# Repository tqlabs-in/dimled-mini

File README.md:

<p align="center">
  <a href="https://github.com/tqlabs-in/dimled-mini">
    <picture>
      <source srcset="assets/logo-dark.png" media="(prefers-color-scheme: dark)">
      <source srcset="assets/logo-light.png" media="(prefers-color-scheme: light)">
      
    </picture>
  </a>
</p>

<p align="center"><q style="font-style: italic; font-weight: bold;"> Open Source PWM LED Dimmer powered by ESPHome </q></p>
<p align="center">
  <a href=""></img></a>
  
</p>

## 😎 Product Photography

## 🎰 PCB Renders

## 🧲 Useful Links

- [Web Flasher](https://tqlabs-in.github.io/dimled-mini/)
- [BOM](https://htmlpreview.github.io/?https://raw.githubusercontent.com/tqlabs-in/dimled-mini/main/pcb/bom/ibom.html)

## 🍀 Show your Support

Give a ⭐️ if this project helped you or you find it interesting!

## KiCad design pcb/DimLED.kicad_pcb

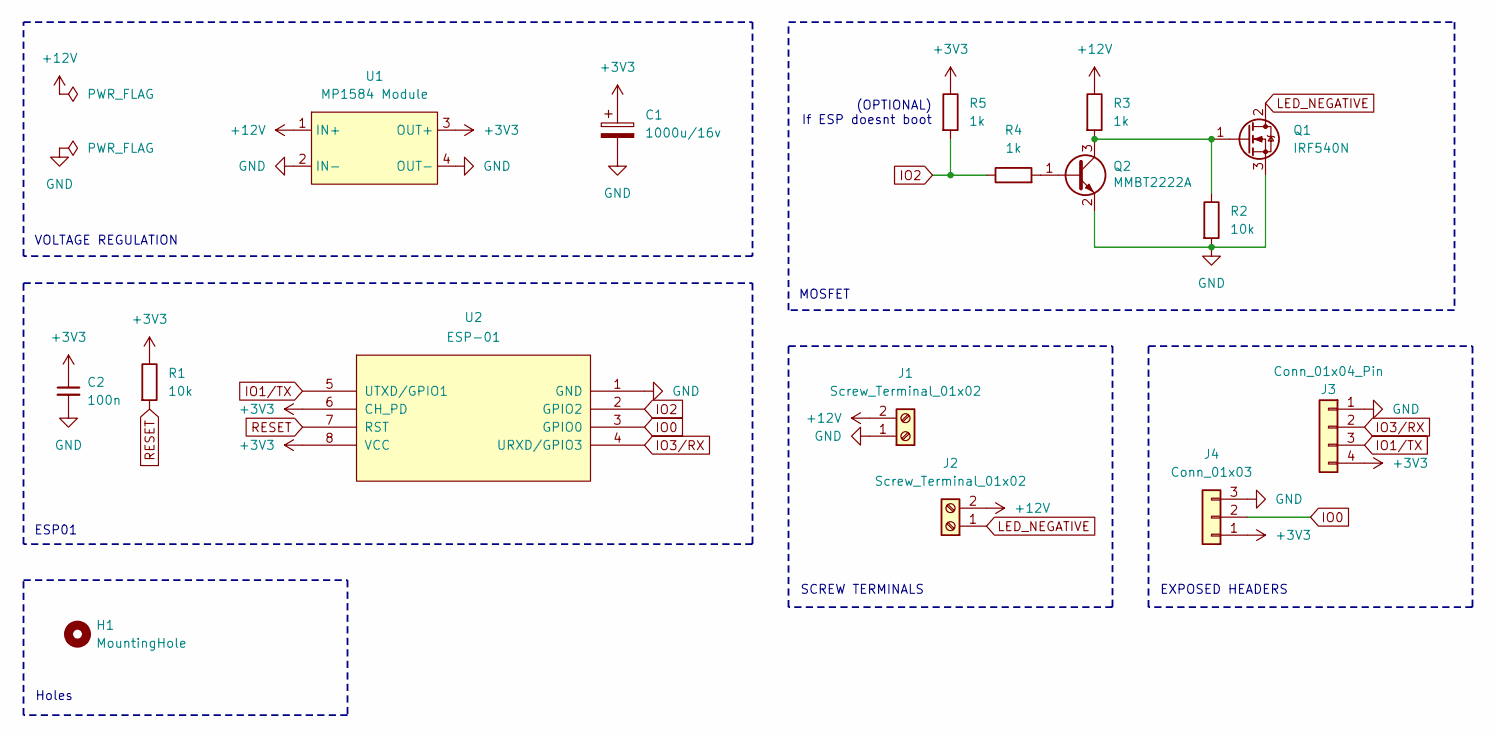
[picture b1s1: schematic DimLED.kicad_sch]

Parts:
C1: 1000u/16v; CP_Radial_D8.0mm_P3.50mm
C2: 100n; C_0805_2012Metric_Pad1.18x1.45mm_HandSolder
H1: MountingHole; ToolingHole_1.152mm
J1, J2: Screw_Terminal_01x02; TerminalBlock_bornier-2_P5.08mm
J3: Conn_01x04_Pin; PinSocket_1x04_P2.54mm_Vertical
J4: Conn_01x03; PinHeader_1x03_P2.54mm_Vertical
Q1: IRF540N; TO-220-3_Vertical
Q2: MMBT2222A; SOT-23
R1, R2: 10k; R_0805_2012Metric_Pad1.20x1.40mm_HandSolder
R3: 1k; R_Axial_DIN0309_L9.0mm_D3.2mm_P2.54mm_Vertical
R4, R5: 1k; R_0805_2012Metric_Pad1.20x1.40mm_HandSolder
U1: MP1584 Module; MP1584-Module_22.1x16.8mm_THT
U2: ESP-01; ESP-01_With_Headers

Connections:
+3V3: C1.1, C2.1, J3.4, J4.1, R1.1, R5.1, U1.3 (OUT+), U2.6 (CH_PD), U2.8 (VCC)
+12V: J1.2, J2.2, R3.1, U1.1 (IN+)
GND: C1.2, C2.2, J1.1, J3.1, J4.3, Q1.3 (S), Q2.2 (E), R2.2, U1.2 (IN-), U1.4 (OUT-), U2.1 (GND)
IO0: J4.2, U2.3 (GPIO0)
IO1/TX: J3.3, U2.5 (UTXD/GPIO1)
IO2: R4.1, R5.2, U2.2 (GPIO2)
IO3/RX: J3.2, U2.4 (URXD/GPIO3)
LED_NEGATIVE: J2.1, Q1.2 (D)
unnamed: Q1.1 (G), Q2.3 (C), R2.1, R3.2
unnamed: Q2.1 (B), R4.2
RESET: R1.2, U2.7 (RST)

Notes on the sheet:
Holes
(OPTIONAL) If ESP doesnt boot
ESP01
VOLTAGE REGULATION
EXPOSED HEADERS
MOSFET
SCREW TERMINALS

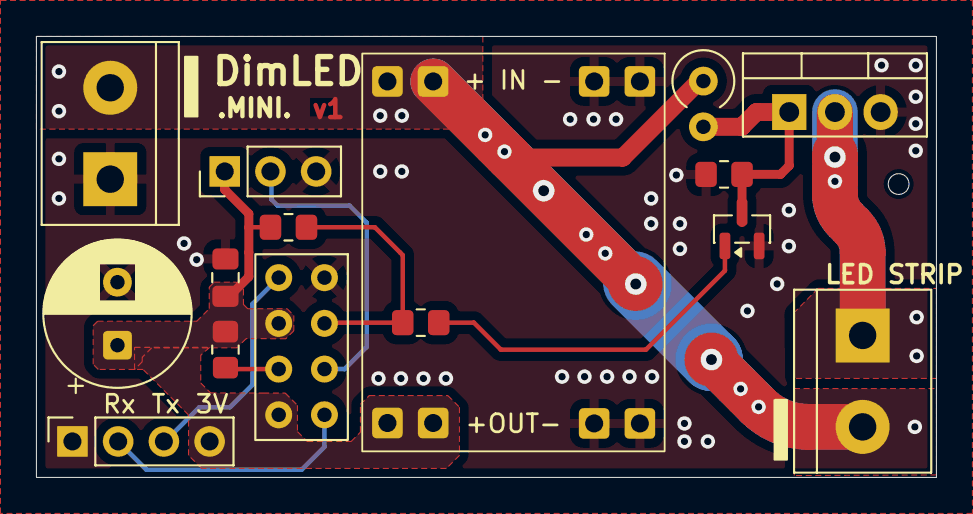
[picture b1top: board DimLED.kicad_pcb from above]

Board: 2 copper layers, 50.0 x 24.5 mm, 16 parts (0 on the bottom side), 11 nets.

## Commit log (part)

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2026-01-07 feat: init
2026-01-07 chore: update logo images
2026-01-07 fix(esphome): ota version replacement
2026-01-07 ci: new action to release on demand
2026-01-07 ci: draft release only
2026-01-07 fix(esphome): ota version
2026-01-07 ci: fix workflow
2026-01-08 refactor(esphome): extendable wifi actions
2026-01-08 fix(esphome): remote web server compile
2026-01-08 fix(esphome): fallback to esphome webserver for now
2026-01-11 ci: host custom webserver js on pages
2026-01-11 docs: add product images
2026-01-14 chore(deps): bump actions/download-artifact from 4.3.0 to 7.0.0
    Bumps [actions/download-artifact](https://github.com/actions/download-artifact) from 4.3.0 to 7.0.0.
    - [Release notes](https://github.com/actions/download-artifact/releases)
    - [Commits](https://github.com/actions/download-artifact/compare/d3f86a106a0bac45b974a628896c90dbdf5c8093...37930b1c2abaa49bbe596cd826c3c89aef350131)
    ---
    updated-dependencies:
    - dependency-name: actions/download-artifact
2026-01-14 chore(deps): bump softprops/action-gh-release from 2.3.3 to 2.5.0
    Bumps [softprops/action-gh-release](https://github.com/softprops/action-gh-release) from 2.3.3 to 2.5.0.
    - [Release notes](https://github.com/softprops/action-gh-release/releases)
    - [Changelog](https://github.com/softprops/action-gh-release/blob/master/CHANGELOG.md)
    - [Commits](https://github.com/softprops/action-gh-release/compare/6cbd405e2c4e67a21c47fa9e383d020e4e28b836...a06a81a03ee405af7f2048a818ed3f03bbf83c7b)
    ---
    updated-dependencies:
2026-01-16 chore: rename
    example -> examples
2026-02-17 fix(esphome): substitutions for ap and wifi
2026-03-04 chore(deps): bump actions/download-artifact from 4.3.0 to 8.0.0
    Bumps [actions/download-artifact](https://github.com/actions/download-artifact) from 4.3.0 to 8.0.0.
    - [Release notes](https://github.com/actions/download-artifact/releases)
    - [Commits](https://github.com/actions/download-artifact/compare/d3f86a106a0bac45b974a628896c90dbdf5c8093...70fc10c6e5e1ce46ad2ea6f2b72d43f7d47b13c3)
    ---
    updated-dependencies:
    - dependency-name: actions/download-artifact
2026-03-17 fix(esphome): mac suffix resolution
2026-03-17 feat(esphome): substitution for mac suffix
2026-03-17 chore: update case
2026-03-18 chore(deps): bump actions/download-artifact from 4.3.0 to 8.0.1
    Bumps [actions/download-artifact](https://github.com/actions/download-artifact) from 4.3.0 to 8.0.1.
    - [Release notes](https://github.com/actions/download-artifact/releases)
    - [Commits](https://github.com/actions/download-artifact/compare/d3f86a106a0bac45b974a628896c90dbdf5c8093...3e5f45b2cfb9172054b4087a40e8e0b5a5461e7c)
    ---
    updated-dependencies:
    - dependency-name: actions/download-artifact
2026-03-18 chore(deps): bump softprops/action-gh-release from 2.5.0 to 2.6.1
    Bumps [softprops/action-gh-release](https://github.com/softprops/action-gh-release) from 2.5.0 to 2.6.1.
    - [Release notes](https://github.com/softprops/action-gh-release/releases)
    - [Changelog](https://github.com/softprops/action-gh-release/blob/master/CHANGELOG.md)
    - [Commits](https://github.com/softprops/action-gh-release/compare/a06a81a03ee405af7f2048a818ed3f03bbf83c7b...153bb8e04406b158c6c84fc1615b65b24149a1fe)
    ---
    updated-dependencies:
2026-04-01 chore(deps): bump actions/deploy-pages from 4 to 5
    Bumps [actions/deploy-pages](https://github.com/actions/deploy-pages) from 4 to 5.
    - [Release notes](https://github.com/actions/deploy-pages/releases)
    - [Commits](https://github.com/actions/deploy-pages/compare/v4...v5)
    ---
    updated-dependencies:
    - dependency-name: actions/deploy-pages
2026-04-01 chore(deps): bump actions/configure-pages from 5 to 6
    Bumps [actions/configure-pages](https://github.com/actions/configure-pages) from 5 to 6.
    - [Release notes](https://github.com/actions/configure-pages/releases)
    - [Commits](https://github.com/actions/configure-pages/compare/v5...v6)
    ---
    updated-dependencies:
    - dependency-name: actions/configure-pages
2026-04-15 chore(deps): bump esphome/workflows/.github/workflows/build.yml
    Bumps [esphome/workflows/.github/workflows/build.yml](https://github.com/esphome/workflows) from 2025.10.0 to 2026.4.0.
    - [Release notes](https://github.com/esphome/workflows/releases)
    - [Commits](https://github.com/esphome/workflows/compare/2025.10.0...2026.4.0)
    ---
    updated-dependencies:
    - dependency-name: esphome/workflows/.github/workflows/build.yml
2026-04-15 chore(deps): bump softprops/action-gh-release from 2.5.0 to 3.0.0
    Bumps [softprops/action-gh-release](https://github.com/softprops/action-gh-release) from 2.5.0 to 3.0.0.
    - [Release notes](https://github.com/softprops/action-gh-release/releases)
    - [Changelog](https://github.com/softprops/action-gh-release/blob/master/CHANGELOG.md)
    - [Commits](https://github.com/softprops/action-gh-release/compare/a06a81a03ee405af7f2048a818ed3f03bbf83c7b...b4309332981a82ec1c5618f44dd2e27cc8bfbfda)
    ---
    updated-dependencies:
2026-04-28 chore: update logo
2026-04-28 docs: change logo width
    Added width attribute to the logo image for better responsiveness.
2026-04-29 chore(deps): bump actions/upload-pages-artifact from 4 to 5
    Bumps [actions/upload-pages-artifact](https://github.com/actions/upload-pages-artifact) from 4 to 5.
    - [Release notes](https://github.com/actions/upload-pages-artifact/releases)
    - [Commits](https://github.com/actions/upload-pages-artifact/compare/v4...v5)
    ---
    updated-dependencies:
    - dependency-name: actions/upload-pages-artifact
2026-05-06 chore(deps): bump esphome/workflows/.github/workflows/build.yml
    Bumps [esphome/workflows/.github/workflows/build.yml](https://github.com/esphome/workflows) from 2026.4.0 to 2026.4.1.
    - [Release notes](https://github.com/esphome/workflows/releases)
    - [Commits](https://github.com/esphome/workflows/compare/2026.4.0...2026.4.1)
    ---
    updated-dependencies:
    - dependency-name: esphome/workflows/.github/workflows/build.yml
2026-06-24 chore(deps): bump softprops/action-gh-release from 3.0.0 to 3.0.1
    Bumps [softprops/action-gh-release](https://github.com/softprops/action-gh-release) from 3.0.0 to 3.0.1.
    - [Release notes](https://github.com/softprops/action-gh-release/releases)
    - [Changelog](https://github.com/softprops/action-gh-release/blob/master/CHANGELOG.md)
    - [Commits](https://github.com/softprops/action-gh-release/compare/b4309332981a82ec1c5618f44dd2e27cc8bfbfda...718ea10b132b3b2eba29c1007bb80653f286566b)
    ---
    updated-dependencies:
2026-06-24 chore(deps): bump actions/checkout from 6 to 7
    Bumps [actions/checkout](https://github.com/actions/checkout) from 6 to 7.
    - [Release notes](https://github.com/actions/checkout/releases)
    - [Changelog](https://github.com/actions/checkout/blob/main/CHANGELOG.md)
    - [Commits](https://github.com/actions/checkout/compare/v6...v7)
    ---
    updated-dependencies:
